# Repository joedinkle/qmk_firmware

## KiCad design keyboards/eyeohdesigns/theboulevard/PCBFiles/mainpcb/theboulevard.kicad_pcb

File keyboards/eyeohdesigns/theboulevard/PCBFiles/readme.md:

## The purpose of this project was to make a working PCB compatible with the open source case for The Ave.

## 25 May 2021 Commit
The JST for the unified daughterboard was reversed. This commit fixes that issue and brings the PCB into compliance with the UDB spec.

## Items tested:

All keys tested.

Encoder functionality.

RGB. I used the standard footprint in Kicad for the through hole RGB. When I wired up the RGB I got off Amazon (which didn't have a datasheet) it was in reverse. Once I flipped the RGB, everything worked fine. Be sure to check the datasheet on your light before installing.

## Items I do not intend to test in the near future:

Compatibility with the open source plate. I know that these PCBs fit in the case, but I don't have the time or resources to ensure everything lines up on the plate. I did take some measurements when initially staarting this project, and noticed that although the case had .5u spacing between the left most column and the main key cluster, at least one of the switch plates did not have this spacing. The PCB I designed uses .5u spacing between the left most column and the main key cluster.

## Known issues:

None at this time.

## Future plans:

The through-hole RGB The_Royal designed this PCB to work with is expensive and can't easily be found in bulk. I'll be looking into changing the top PCB to use SMT RGB with a light pipe.

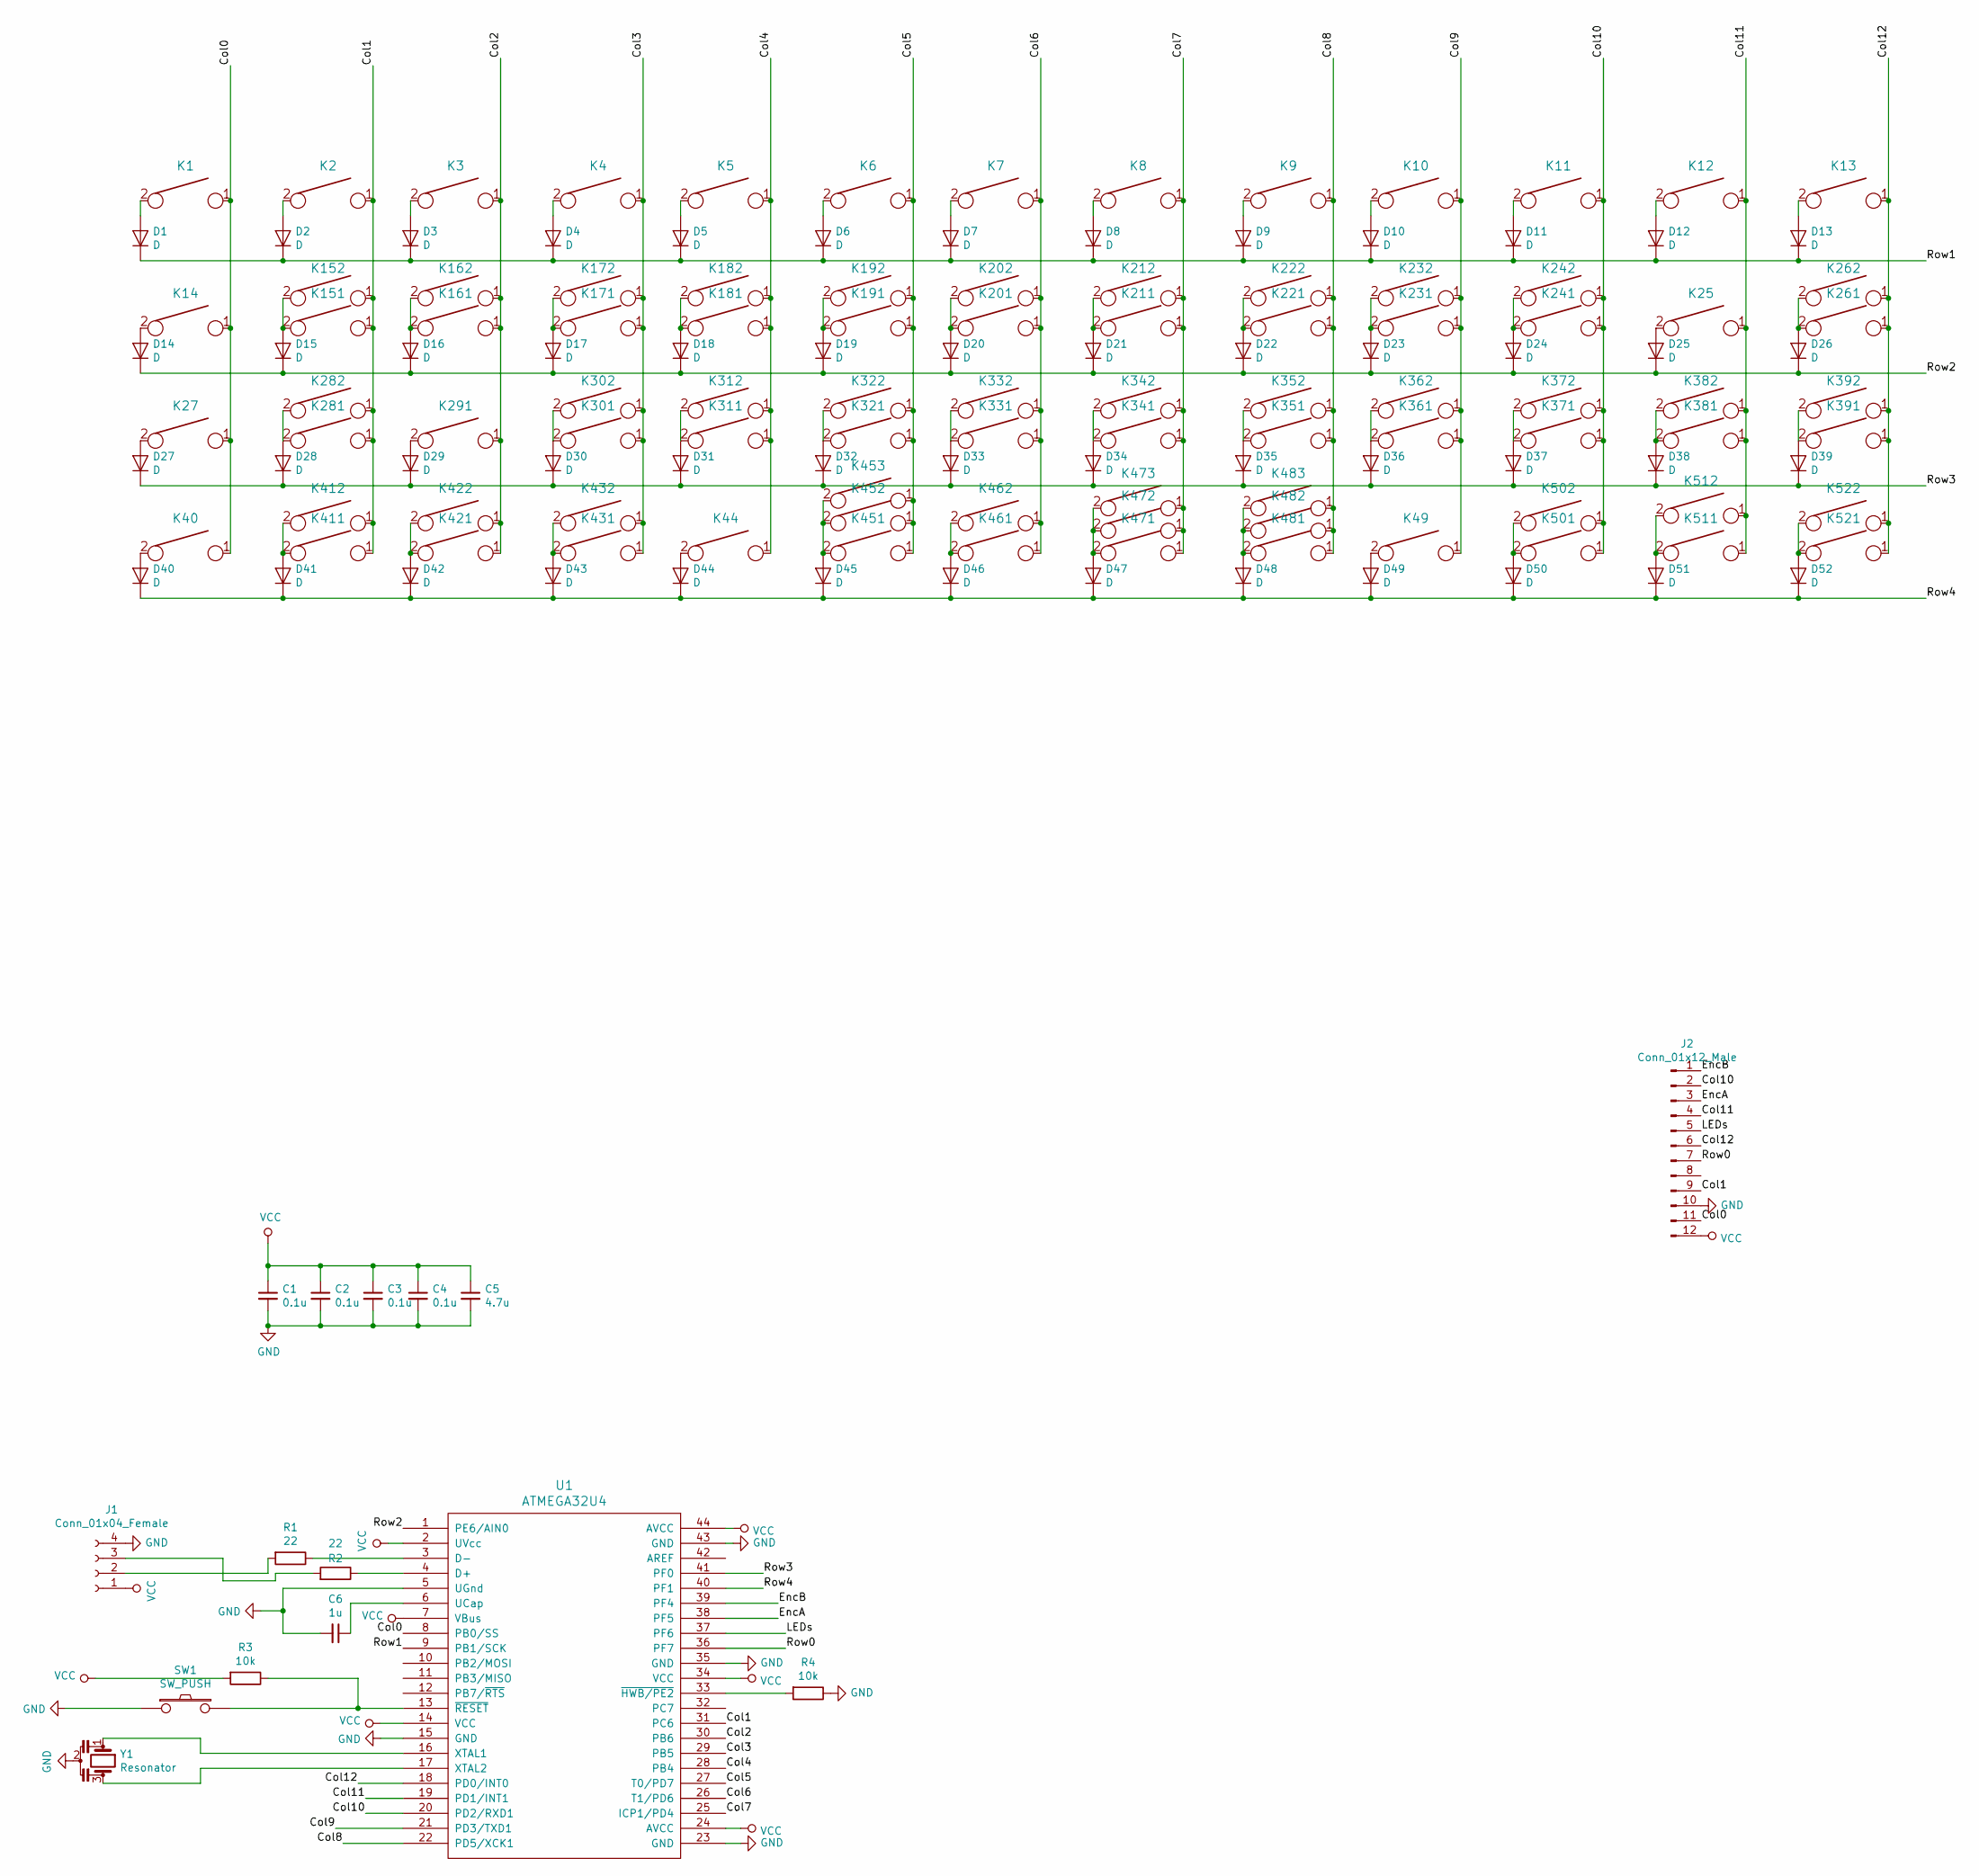
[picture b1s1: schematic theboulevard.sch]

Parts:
C1, C2, C3, C4: 0.1u; C_0603_1608Metric_Pad1.05x0.95mm_HandSolder
C5: 4.7u; C_0603_1608Metric_Pad1.05x0.95mm_HandSolder
C6: 1u; C_0603_1608Metric_Pad1.05x0.95mm_HandSolder
D1, D2, D3, D4, D5, D6, D7, D8, D9, D10, D11, D12, D13, D14, D15, D16, D17, D18, D19, D20, D21, D22, D23, D24, D25, D26, D27, D28, D29, D30, D31, D32, D33, D34, D35, D36, D37, D38, D39, D40, D41, D42, D43, D44, D45, D46, D47, D48, D49, D50, D51, D52: D; D_SOD123
J1: Conn_01x04_Female; JST_SH_SM04B-SRSS-TB_1x04-1MP_P1.00mm_Horizontal
J2: Conn_01x12_Male; PinHeader_2x06_P2.00mm_Horizontal
K1, K2, K3, K4, K5, K6, K7, K8, K9, K10, K11, K12, K13, K14, K25, K27, K40, K44, K49, K151, K161, K162, K171, K172, K181, K182, K191, K192, K201, K202, K211, K212, K221, K222, K231, K232, K241, K242, K261, K281, K291, K301, K302, K311, K312, K321, K322, K331, K332, K341, K342, K351, K352, K361, K362, K371, K372, K381, K382, K391, K411, K421, K431, K451, K461, K471, K481, K501, K511, K521: KEYSW; SW_Cherry_MX_1.00u_PCB_No_Silk
K152, K392, K412, K432, K502, K522: KEYSW; SW_Cherry_MX_1.25u_PCB_No_Silk
K262, K282: KEYSW; SW_Cherry_MX_1.75u_PCB_No_Silk
K422, K512: KEYSW; SW_Cherry_MX_1.50u_PCB_No_Silk
K452, K473, K483: KEYSW; SW_Cherry_MX_2.00u_PCB_Flip_Stab
K453: KEYSW; MX_2.75u_PCB_No_Silk_Flipped_Stab
K462: KEYSW; MX_6.25u_PCB_Flipped_Stab_No_Silk
K472: KEYSW; SW_Cherry_MX_7u_PCB_No_Silk_Flip_Stab
K482: KEYSW; MX_2.25u_PCB_No_Silk_Flipped_Stab
R1, R2: 22; R_0603_1608Metric_Pad1.05x0.95mm_HandSolder
R3, R4: 10k; R_0603_1608Metric_Pad1.05x0.95mm_HandSolder
SW1: SW_PUSH; SW_SPST_TL3342
U1: ATMEGA32U4; QFN-44-1EP_7x7mm_P0.5mm_EP5.2x5.2mm
Y1: Resonator; Abracon_Resonator_16MHz_22pf

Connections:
/Col0: J2.11, K1.1, K14.1, K27.1, K40.1, U1.8 (PB0/SS)
/Col1: J2.9, K2.1, K151.1, K152.1, K281.1, K282.1, K411.1, K412.1, U1.31 (PC6)
/Col2: K3.1, K161.1, K162.1, K291.1, K421.1, K422.1, U1.30 (PB6)
/Col3: K4.1, K171.1, K172.1, K301.1, K302.1, K431.1, K432.1, U1.29 (PB5)
/Col4: K5.1, K44.1, K181.1, K182.1, K311.1, K312.1, U1.28 (PB4)
/Col5: K6.1, K191.1, K192.1, K321.1, K322.1, K451.1, K452.1, K453.1, U1.27 (T0/PD7)
/Col6: K7.1, K201.1, K202.1, K331.1, K332.1, K461.1, K462.1, U1.26 (T1/PD6)
/Col7: K8.1, K211.1, K212.1, K341.1, K342.1, K471.1, K472.1, K473.1, U1.25 (ICP1/PD4)
/Col8: K9.1, K221.1, K222.1, K351.1, K352.1, K481.1, K482.1, K483.1, U1.22 (PD5/XCK1)
/Col9: K10.1, K49.1, K231.1, K232.1, K361.1, K362.1, U1.21 (PD3/TXD1)
/Col10: J2.2, K11.1, K241.1, K242.1, K371.1, K372.1, K501.1, K502.1, U1.20 (PD2/RXD1)
/Col11: J2.4, K12.1, K25.1, K381.1, K382.1, K511.1, K512.1, U1.19 (PD1/INT1)
/Col12: J2.6, K13.1, K261.1, K262.1, K391.1, K392.1, K521.1, K522.1, U1.18 (PD0/INT0)
/EncA: J2.3, U1.38 (PF5)
/EncB: J2.1, U1.39 (PF4)
/LEDs: J2.5, U1.37 (PF6)
/Row0: J2.7, U1.36 (PF7)
/Row1: D1.1 (K), D2.1 (K), D3.1 (K), D4.1 (K), D5.1 (K), D6.1 (K), D7.1 (K), D8.1 (K), D9.1 (K), D10.1 (K), D11.1 (K), D12.1 (K), D13.1 (K), U1.9 (PB1/SCK)
/Row2: D14.1 (K), D15.1 (K), D16.1 (K), D17.1 (K), D18.1 (K), D19.1 (K), D20.1 (K), D21.1 (K), D22.1 (K), D23.1 (K), D24.1 (K), D25.1 (K), D26.1 (K), U1.1 (PE6/AIN0)
/Row3: D27.1 (K), D28.1 (K), D29.1 (K), D30.1 (K), D31.1 (K), D32.1 (K), D33.1 (K), D34.1 (K), D35.1 (K), D36.1 (K), D37.1 (K), D38.1 (K), D39.1 (K), U1.41 (PF0)
/Row4: D40.1 (K), D41.1 (K), D42.1 (K), D43.1 (K), D44.1 (K), D45.1 (K), D46.1 (K), D47.1 (K), D48.1 (K), D49.1 (K), D50.1 (K), D51.1 (K), D52.1 (K), U1.40 (PF1)
GND: C1.2, C2.2, C3.2, C4.2, C5.2, C6.2, J1.4, J2.10, R4.1, SW1.1, U1.5 (UGnd), U1.15 (GND), U1.23 (GND), U1.35 (GND), U1.43 (GND), Y1.2
unnamed: C6.1, U1.6 (UCap)
unnamed: D1.2 (A), K1.2
unnamed: D2.2 (A), K2.2
unnamed: D3.2 (A), K3.2
unnamed: D4.2 (A), K4.2
unnamed: D5.2 (A), K5.2
unnamed: D6.2 (A), K6.2
unnamed: D7.2 (A), K7.2
unnamed: D8.2 (A), K8.2
unnamed: D9.2 (A), K9.2
unnamed: D10.2 (A), K10.2
unnamed: D11.2 (A), K11.2
unnamed: D12.2 (A), K12.2
unnamed: D13.2 (A), K13.2
unnamed: D14.2 (A), K14.2
unnamed: D15.2 (A), K151.2, K152.2
unnamed: D16.2 (A), K161.2, K162.2
unnamed: D17.2 (A), K171.2, K172.2
unnamed: D18.2 (A), K181.2, K182.2
unnamed: D19.2 (A), K191.2, K192.2
unnamed: D20.2 (A), K201.2, K202.2
unnamed: D21.2 (A), K211.2, K212.2
unnamed: D22.2 (A), K221.2, K222.2
unnamed: D23.2 (A), K231.2, K232.2
unnamed: D24.2 (A), K241.2, K242.2
unnamed: D25.2 (A), K25.2
unnamed: D26.2 (A), K261.2, K262.2
unnamed: D27.2 (A), K27.2
unnamed: D28.2 (A), K281.2, K282.2
unnamed: D29.2 (A), K291.2
unnamed: D30.2 (A), K301.2, K302.2
unnamed: D31.2 (A), K311.2, K312.2
unnamed: D32.2 (A), K321.2, K322.2
unnamed: D33.2 (A), K331.2, K332.2
unnamed: D34.2 (A), K341.2, K342.2
unnamed: D35.2 (A), K351.2, K352.2
unnamed: D36.2 (A), K361.2, K362.2
unnamed: D37.2 (A), K371.2, K372.2
unnamed: D38.2 (A), K381.2, K382.2
unnamed: D39.2 (A), K391.2, K392.2
unnamed: D40.2 (A), K40.2
unnamed: D41.2 (A), K411.2, K412.2
unnamed: D42.2 (A), K421.2, K422.2
unnamed: D43.2 (A), K431.2, K432.2
unnamed: D44.2 (A), K44.2
unnamed: D45.2 (A), K451.2, K452.2, K453.2
unnamed: D46.2 (A), K461.2, K462.2
unnamed: D47.2 (A), K471.2, K472.2, K473.2
unnamed: D48.2 (A), K481.2, K482.2, K483.2
unnamed: D49.2 (A), K49.2
unnamed: D50.2 (A), K501.2, K502.2
unnamed: D51.2 (A), K511.2, K512.2
unnamed: D52.2 (A), K521.2, K522.2
unnamed: J1.2, R1.2
unnamed: J1.3, R2.2
unnamed: R1.1, U1.3 (D-)
unnamed: R2.1, U1.4 (D+)
unnamed: R3.1, SW1.2, U1.13 (~RESET)
unnamed: R4.2, U1.33 (~HWB/PE2)
unnamed: U1.16 (XTAL1), Y1.1
unnamed: U1.17 (XTAL2), Y1.3
VCC: C1.1, C2.1, C3.1, C4.1, C5.1, J1.1, J2.12, R3.2, U1.2 (UVcc), U1.7 (VBus), U1.14 (VCC), U1.24 (AVCC), U1.34 (VCC), U1.44 (AVCC)

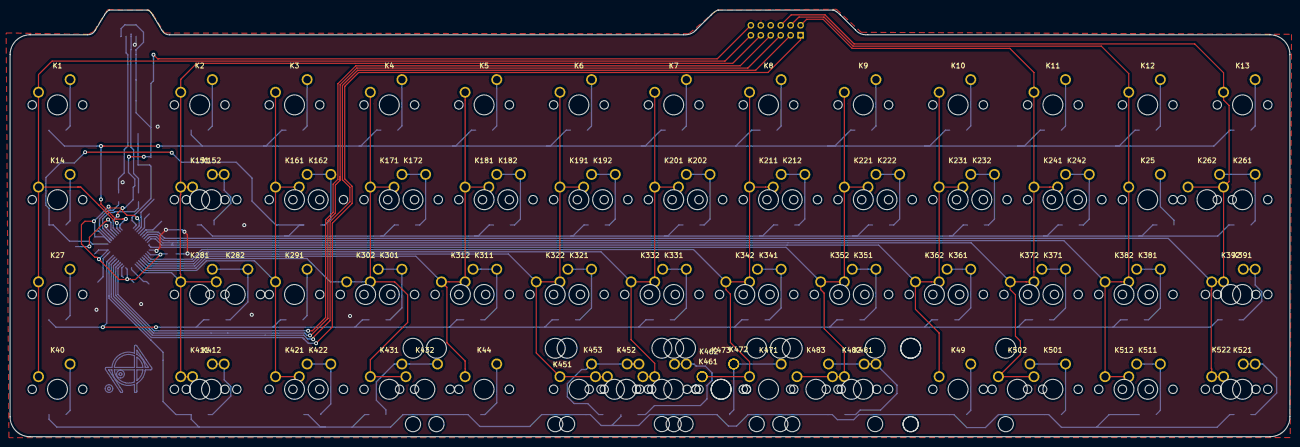
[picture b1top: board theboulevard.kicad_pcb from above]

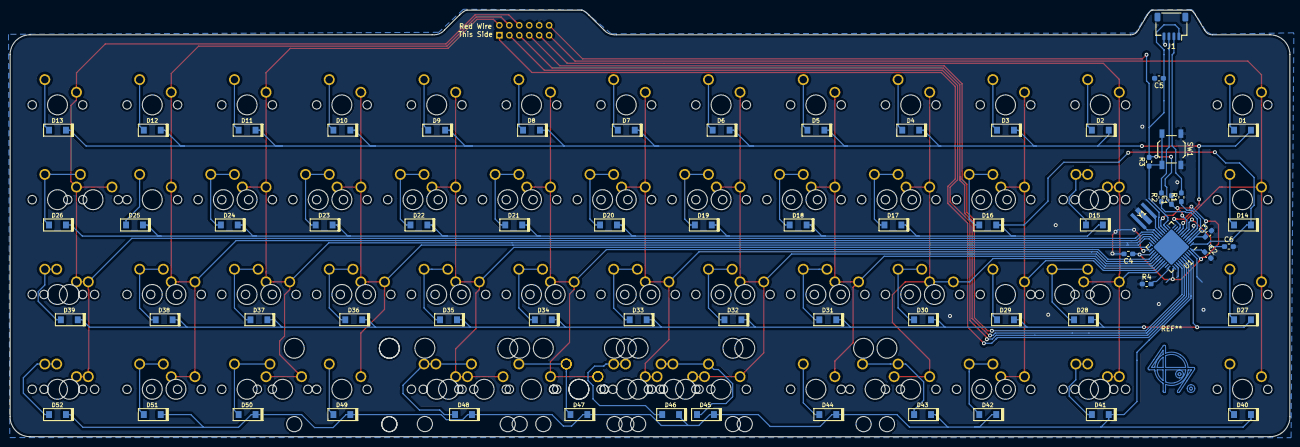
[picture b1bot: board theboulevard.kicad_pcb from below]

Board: 2 copper layers, 257.2 x 85.7 mm, 154 parts (67 on the bottom side), 84 nets.

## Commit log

2020-07-11 Update keymap.c
    Add formatting to raise keymap
2020-12-15 Add SPRH Prototype Test map.
2021-05-25 Fixes a reversed connector on the main PCB
2021-06-03 initial commit for humble40
2021-06-03 removed files not related to humble40
2021-06-03 clarified default keymap
2021-06-03 readme update
2021-06-13 Added case files
2021-06-13 moved and updated readme
